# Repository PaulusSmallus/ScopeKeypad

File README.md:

# ScopeKeypad
This project is to create a traditional oscilloscope interface to use with the PicoScope software (or more generally other usb scopes).
It's useful for people who are more comfortable with traditional oscilloscope buttons and dials.

https://youtu.be/zDIKAT928zg

It uses an STM32 (arduino 'bluepill') as the main processor. It acts as a keyboard, so pressing buttons or rotating dials just sends keyboard shortcuts to the PC over USB.

To use:

Make circuit

	- get the 'main_pcb' made. (in the Hardware\gerbers folder)
	
	- get one of the 'front_panels' made. There is one for 7mm buttons, and one for 12mm buttons.
	
	- Solder all the components on
	
	- Solder JP1 and JP2 depending on if you brought Sparkfun or Worldsemi LEDs (they have different pinouts -_- ).

upload firmware

	- Install Arduino_STM32 ( https://github.com/rogerclarkmelbourne/Arduino_STM32 )
	
	- Open ScopeKeypad\Firmware\ScopeKeypad_Firmware\ScopeKeypad_Firmware.ino
	
	- Upload firmware with settings:
	
		- Board: "Generic STM32F103C"
		
		- Variant: "STM32F103C8 (20k RAM, 65k Flash)"
		
		- Upload method: "STLink"
		
		- CPU Speed(MHz): "72Mhz (normal)"
		
		- Optimize: "Smallest (default)"

upload shortcut settings to PicoScope software

	- Open PicoScope
	
	- Click 'Tools'
	
	- Click 'Preferences...'
	
	- Open the 'Keyboard' tab
	
	- Under 'Select keyboard map.', select 'import'
	
	- Open 'Software\picoscope_shortcuts.pskeys'

TODO:

	- change keyboard shortcuts from using 'Alt', as this sometimes causes issues. Use 'Ctrl' and 'Shift' only.

How it all works:

	The encoders are connected to hardware interrupts, which keep track of the position.
	
	The buttons are connected in a matrix.
	
	The firmware then checks for any changes, and sends keyboard shortcuts.

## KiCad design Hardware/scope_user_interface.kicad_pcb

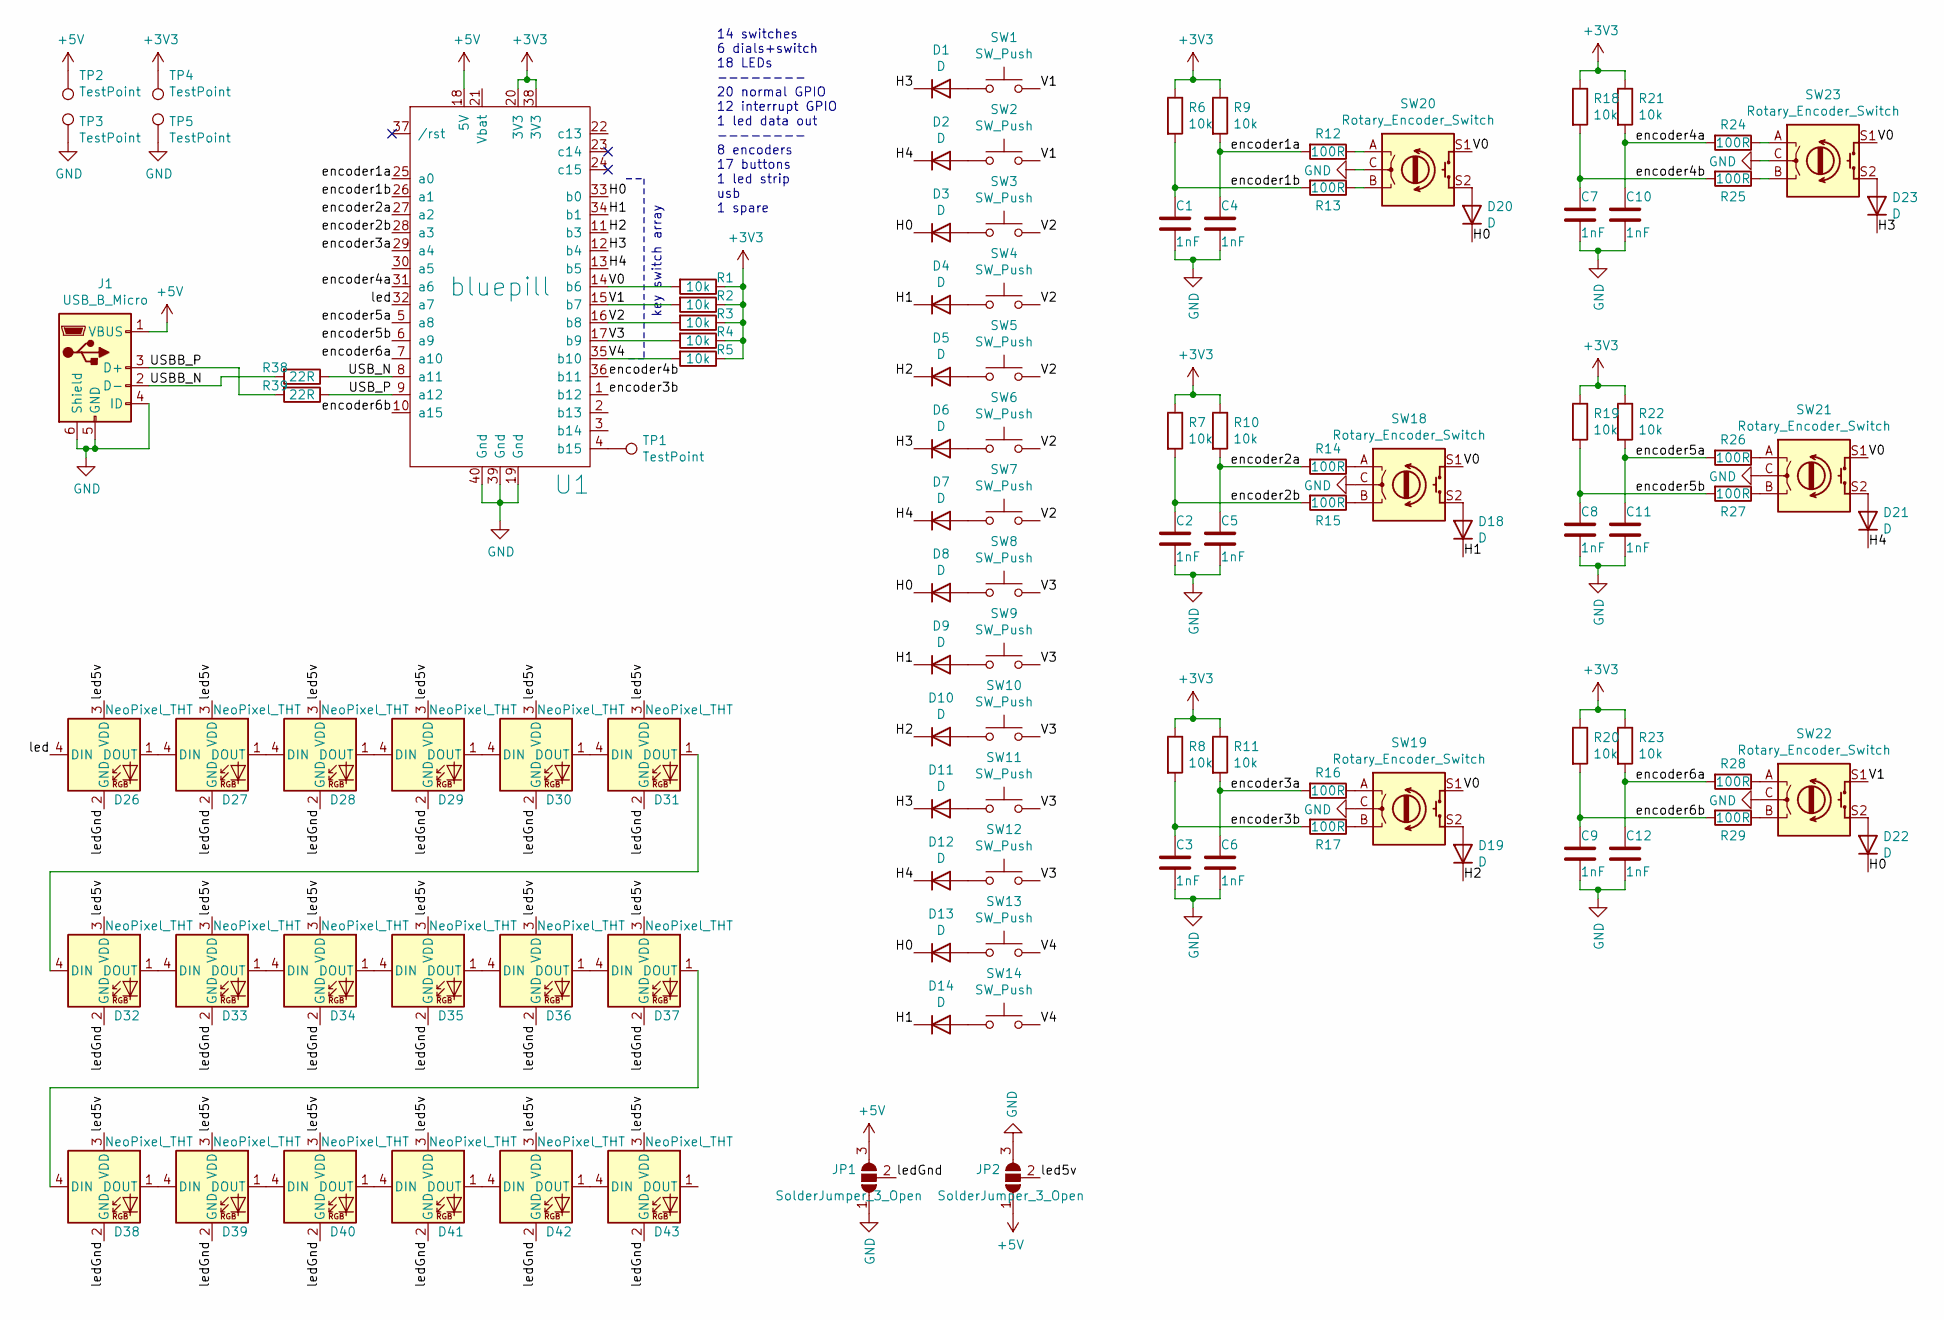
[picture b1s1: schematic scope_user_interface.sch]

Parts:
C1, C2, C3, C4, C5, C6, C7, C8, C9, C10, C11, C12: 1nF; C_0805_2012Metric
D1, D2, D3, D4, D5, D6, D7, D8, D9, D10, D11, D12, D13, D14, D18, D19, D20, D21, D22, D23: D; D_SOD-123F
D26, D27, D28, D29, D30, D31, D32, D33, D34, D35, D36, D37, D38, D39, D40, D41, D42, D43: NeoPixel_THT; LED_D5.0mm-4_RGB
J1: USB_B_Micro; USB_Micro-B_Molex_47346-0001
JP1, JP2: SolderJumper_3_Open; SolderJumper-3_P1.3mm_Open_RoundedPad1.0x1.5mm
R1, R2, R3, R4, R5, R6, R7, R8, R9, R10, R11, R18, R19, R20, R21, R22, R23: 10k; R_0805_2012Metric
R12, R13, R14, R15, R16, R17, R24, R25, R26, R27, R28, R29: 100R; R_0805_2012Metric
R38, R39: 22R; R_0805_2012Metric
SW1, SW2, SW3, SW4, SW5, SW6, SW7, SW8, SW9, SW10, SW11, SW12, SW13, SW14: SW_Push; SW_PUSH-12mm
SW18, SW19, SW20, SW21, SW22, SW23: Rotary_Encoder_Switch; RotaryEncoder_Alps_EC11E-Switch_Vertical_H20mm
TP1, TP2, TP3, TP4, TP5: TestPoint; TestPoint_Loop_D2.50mm_Drill1.85mm
U1: bluepill; DIP-40_15.24_generic

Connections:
+3V3: R1.1, R2.1, R3.1, R4.1, R5.1, R6.1, R7.1, R8.1, R9.1, R10.1, R11.1, R18.1, R19.1, R20.1, R21.1, R22.1, R23.1, TP4.1, U1.20 (3V3), U1.38 (3V3)
+5V: J1.1 (VBUS), JP1.3 (B), JP2.1 (A), TP2.1, U1.18 (5V)
/H0: D3.1 (K), D8.1 (K), D13.1 (K), D20.1 (K), D22.1 (K), U1.33 (b0)
/H1: D4.1 (K), D9.1 (K), D14.1 (K), D18.1 (K), U1.34 (b1)
/H2: D5.1 (K), D10.1 (K), D19.1 (K), U1.11 (b3)
/H3: D1.1 (K), D6.1 (K), D11.1 (K), D23.1 (K), U1.12 (b4)
/H4: D2.1 (K), D7.1 (K), D12.1 (K), D21.1 (K), U1.13 (b5)
/USBB_N: J1.2 (D-), R38.2
/USBB_P: J1.3 (D+), R39.2
/USB_N: R38.1, U1.8 (a11)
/USB_P: R39.1, U1.9 (a12)
/V0: R1.2, SW18.S1, SW19.S1, SW20.S1, SW21.S1, SW23.S1, U1.14 (b6)
/V1: R2.2, SW1.2, SW2.2, SW22.S1, U1.15 (b7)
/V2: R3.2, SW3.2, SW4.2, SW5.2, SW6.2, SW7.2, U1.16 (b8)
/V3: R4.2, SW8.2, SW9.2, SW10.2, SW11.2, SW12.2, U1.17 (b9)
/V4: R5.2, SW13.2, SW14.2, U1.35 (b10)
/encoder1a: C4.1, R9.2, R12.2, U1.25 (a0)
/encoder1b: C1.1, R6.2, R13.2, U1.26 (a1)
/encoder2a: C5.1, R10.2, R14.2, U1.27 (a2)
/encoder2b: C2.1, R7.2, R15.2, U1.28 (a3)
/encoder3a: C6.1, R11.2, R16.2, U1.29 (a4)
/encoder3b: C3.1, R8.2, R17.2, U1.1 (b12)
/encoder4a: C10.1, R21.2, R24.2, U1.31 (a6)
/encoder4b: C7.1, R18.2, R25.2, U1.36 (b11)
/encoder5a: C11.1, R22.2, R26.2, U1.5 (a8)
/encoder5b: C8.1, R19.2, R27.2, U1.6 (a9)
/encoder6a: C12.1, R23.2, R28.2, U1.7 (a10)
/encoder6b: C9.1, R20.2, R29.2, U1.10 (a15)
/led: D26.4 (DIN), U1.32 (a7)
/led5v: D26.3 (VDD), D27.3 (VDD), D28.3 (VDD), D29.3 (VDD), D30.3 (VDD), D31.3 (VDD), D32.3 (VDD), D33.3 (VDD), D34.3 (VDD), D35.3 (VDD), D36.3 (VDD), D37.3 (VDD), D38.3 (VDD), D39.3 (VDD), D40.3 (VDD), D41.3 (VDD), D42.3 (VDD), D43.3 (VDD), JP2.2 (C)
/ledGnd: D26.2 (GND), D27.2 (GND), D28.2 (GND), D29.2 (GND), D30.2 (GND), D31.2 (GND), D32.2 (GND), D33.2 (GND), D34.2 (GND), D35.2 (GND), D36.2 (GND), D37.2 (GND), D38.2 (GND), D39.2 (GND), D40.2 (GND), D41.2 (GND), D42.2 (GND), D43.2 (GND), JP1.2 (C)
GND: C1.2, C2.2, C3.2, C4.2, C5.2, C6.2, C7.2, C8.2, C9.2, C10.2, C11.2, C12.2, J1.4 (ID), J1.5 (GND), J1.6 (Shield), JP1.1 (A), JP2.3 (B), SW18.C, SW19.C, SW20.C, SW21.C, SW22.C, SW23.C, TP3.1, TP5.1, U1.19 (Gnd), U1.39 (Gnd), U1.40 (Gnd); also elsewhere on the board
unnamed: D1.2 (A), SW1.1
unnamed: D2.2 (A), SW2.1
unnamed: D3.2 (A), SW3.1
unnamed: D4.2 (A), SW4.1
unnamed: D5.2 (A), SW5.1
unnamed: D6.2 (A), SW6.1
unnamed: D7.2 (A), SW7.1
unnamed: D8.2 (A), SW8.1
unnamed: D9.2 (A), SW9.1
unnamed: D10.2 (A), SW10.1
unnamed: D11.2 (A), SW11.1
unnamed: D12.2 (A), SW12.1
unnamed: D13.2 (A), SW13.1
unnamed: D14.2 (A), SW14.1
unnamed: D18.2 (A), SW18.S2
unnamed: D19.2 (A), SW19.S2
unnamed: D20.2 (A), SW20.S2
unnamed: D21.2 (A), SW21.S2
unnamed: D22.2 (A), SW22.S2
unnamed: D23.2 (A), SW23.S2
unnamed: D26.1 (DOUT), D27.4 (DIN)
unnamed: D27.1 (DOUT), D28.4 (DIN)
unnamed: D28.1 (DOUT), D29.4 (DIN)
unnamed: D29.1 (DOUT), D30.4 (DIN)
unnamed: D30.1 (DOUT), D31.4 (DIN)
unnamed: D31.1 (DOUT), D32.4 (DIN)
unnamed: D32.1 (DOUT), D33.4 (DIN)
unnamed: D33.1 (DOUT), D34.4 (DIN)
unnamed: D34.1 (DOUT), D35.4 (DIN)
unnamed: D35.1 (DOUT), D36.4 (DIN)
unnamed: D36.1 (DOUT), D37.4 (DIN)
unnamed: D37.1 (DOUT), D38.4 (DIN)
unnamed: D38.1 (DOUT), D39.4 (DIN)
unnamed: D39.1 (DOUT), D40.4 (DIN)
unnamed: D40.1 (DOUT), D41.4 (DIN)
unnamed: D41.1 (DOUT), D42.4 (DIN)
unnamed: D42.1 (DOUT), D43.4 (DIN)
unnamed: R12.1, SW20.A
unnamed: R13.1, SW20.B
unnamed: R14.1, SW18.A
unnamed: R15.1, SW18.B
unnamed: R16.1, SW19.A
unnamed: R17.1, SW19.B
unnamed: R24.1, SW23.A
unnamed: R25.1, SW23.B
unnamed: R26.1, SW21.A
unnamed: R27.1, SW21.B
unnamed: R28.1, SW22.A
unnamed: R29.1, SW22.B
unnamed: TP1.1, U1.4 (b15)

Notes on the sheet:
14 switches 6 dials+switch 18 LEDs -------- 20 normal GPIO 12 interrupt GPIO 1 led data out -------- 8 encoders 17 buttons 1 led strip usb 1 spare
key switch array

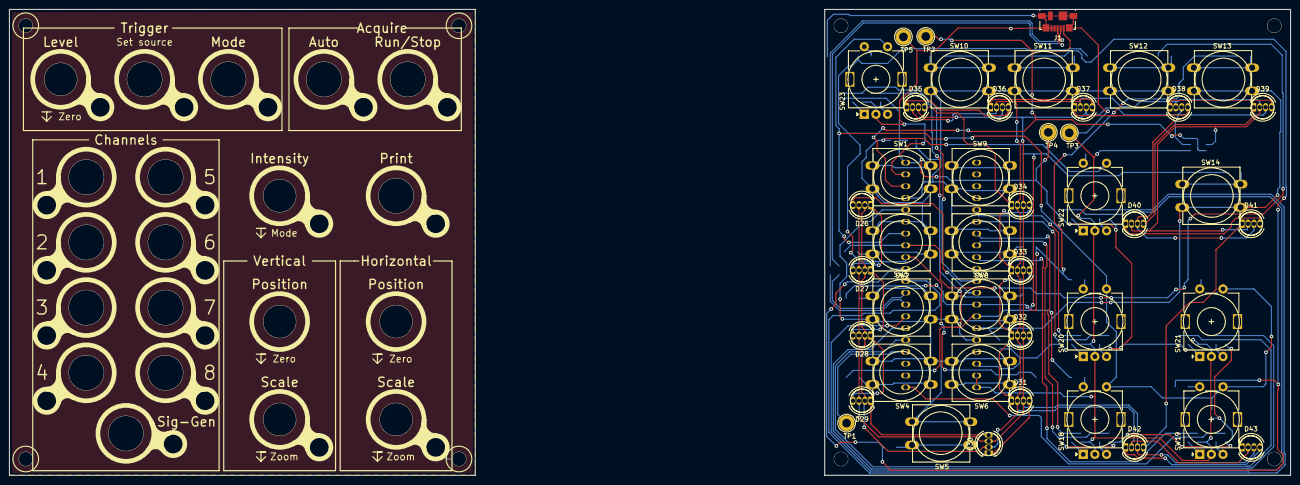
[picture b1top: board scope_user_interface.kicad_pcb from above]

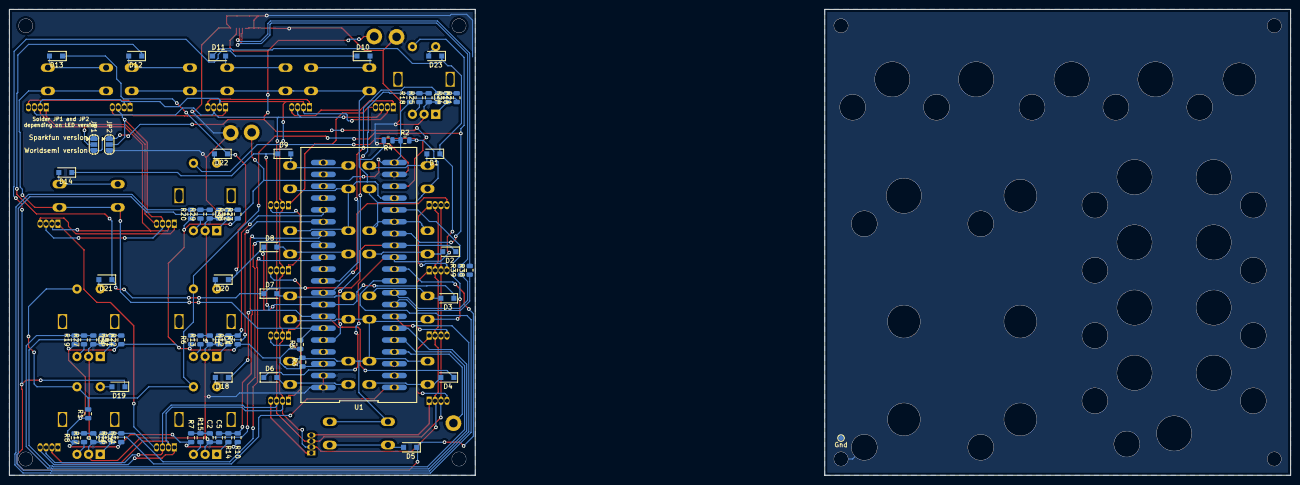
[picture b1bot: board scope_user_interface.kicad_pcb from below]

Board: 2 copper layers, 275.0 x 100.0 mm, 111 parts (67 on the bottom side), 82 nets.

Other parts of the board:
Gnd: TestPoint_Pad_D1.0mm

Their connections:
GND: Gnd.1; also elsewhere on the board

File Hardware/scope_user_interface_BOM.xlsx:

Reference | Quantity | Value | Footprint | Datasheet | Cost ea | Cost total | link | lcsc number | part number
C1 C4 C2 C5 C3 C6 C7 C10 C8 C11 C9 C12 C13 C15 C14 C16 | 16 | 1nF | Capacitor_SMD:C_0805_2012Metric |  | 4.1999999999999997E-3 | 6.7199999999999996E-2 | https://lcsc.com/product-detail/Multilayer-Ceramic-Capacitor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 | C713510 | Generic
D20 D18 D19 D23 D21 D22 D24 D25 D1 D2 D3 D4 D5 D6 D7 D8 D9 D10 D11 D12 D13 D14 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 | 25 | D | Diode_SMD:D_SOD-123F |  | 5.1000000000000004E-3 | 0.1275 | https://lcsc.com/product-detail/Diodes-General-Purpose_Shand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 | C108803 | Generic
D26 D27 D28 D29 D30 D31 D32 D33 D34 D35 D36 D37 D38 D39 D40 D41 D42 D43 | 18 | NeoPixel_THT | LED_THT:LED_D5.0mm-4_RGB | https://www.adafruit.com/product/1938 | 0.1195 | 2.1509999999999998 | https://lcsc.com/product-detail/Others_WS2812D-F5_C190565.html | C190565 | WS2812D-F5
J1 | 1 | USB_B | Connector_USB:USB_B_OST_USB-B1HSxx_Horizontal |  | 0.54549999999999998 | 0.54549999999999998 | https://lcsc.com/product-detail/USB-Connectors_MOLEX_47346-0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 | C132560 | MOLEX 473460001
R12 R13 R14 R15 R16 R17 R24 R25 R26 R27 R28 R29 R34 R35 R36 R37 | 16 | 100R | Resistor_SMD:R_0805_2012Metric |  |  | 0 |  |  | generic
R38 R39 | 2 | 22R | Resistor_SMD:R_0805_2012Metric |  |  | 0 |  |  | generic
R9 R6 R10 R7 R11 R8 R21 R18 R22 R19 R23 R20 R32 R30 R33 R31 R1 R2 R3 R4 R5 | 21 | 10k | Resistor_SMD:R_0805_2012Metric |  |  | 0 |  |  | generic
SW1 SW2 SW3 SW4 SW5 SW6 SW7 SW8 SW9 SW10 SW11 SW12 SW13 SW14 SW15 SW16 SW17 | 17 | SW_Push | Button_Switch_THT:SW_PUSH-12mm |  | 5.8000000000000003E-2 | 0.9860000000000001 | https://lcsc.com/product-detail/Tactile-Switches_USAKRO-UK-B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 | C780506UK-B0224-G9-250 | C780506
SW20 SW18 SW19 SW23 SW21 SW22 SW25 SW24 | 8 | Rotary_Encoder_Switch | Rotary_Encoder:RotaryEncoder_Alps_EC11E-Switch_Vertical_H20mm | ~ | 1.6681999999999999 | 13.345599999999999 | https://lcsc.com/product-detail/Coded-Rotary-Switches_ALPS-E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 | C470753 | EC11E09244AQ
TP1 | 1 | TestPoint |  | ~ |  | 0
U1 | 1 | bluepill | footprints:DIP-40_15.24_generic |  |  | 0 |  | aliexpress?
 |  |  | rotary dial cap
 |  |  |  |  | TOTAL | 17.222799999999999

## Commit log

2021-01-18 first upload
2021-01-18 main upload
2021-01-19 Revert "Update README.md"
    This reverts commit 3edde7b1d6cc46fb0cd567663e1a1fd710ba3a38.
2021-01-19 added schematic pdf
2021-01-19 Changed encoder3b to PB12
2021-01-21 added more details to readme
2021-01-26 updated readme for better english
2023-12-17 update for picoscope
